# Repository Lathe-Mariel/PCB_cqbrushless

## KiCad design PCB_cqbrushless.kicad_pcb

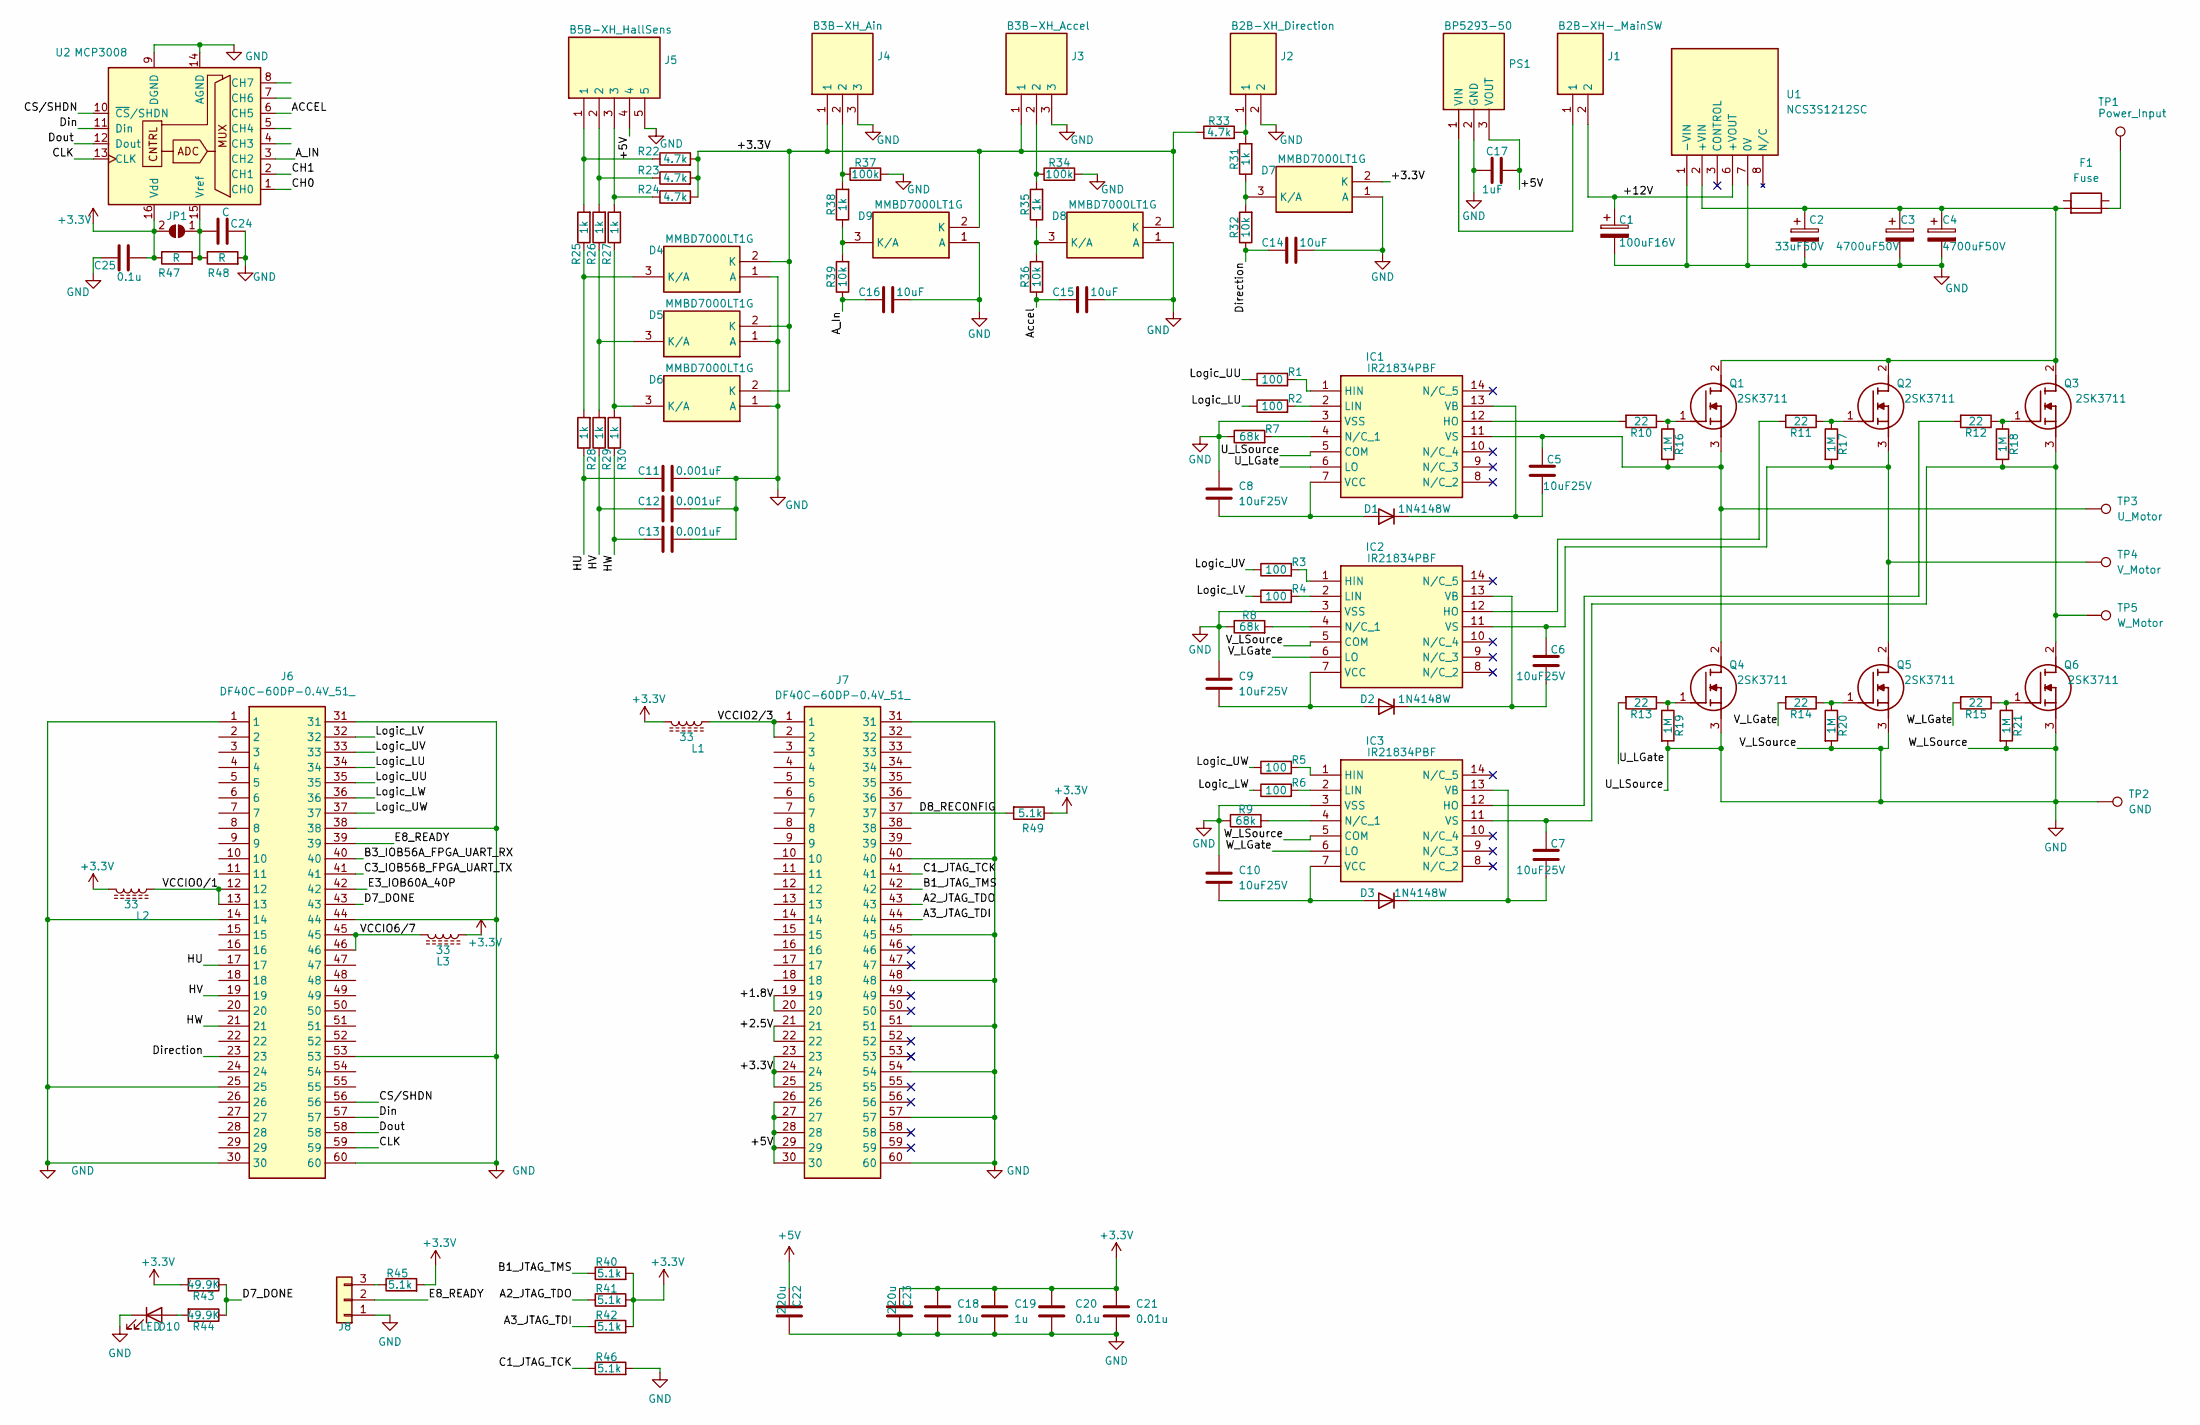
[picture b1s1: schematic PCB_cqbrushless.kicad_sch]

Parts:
C1: 100uF16V; CP_Radial_D5.0mm_P2.00mm
C2: 33uF50V; CP_Radial_D5.0mm_P2.00mm
C3, C4: 4700uF50V; CP_Radial_D35.0mm_P10.00mm_SnapIn
C5, C6, C7, C8, C9, C10: 10uF25V; C_0603_1608Metric_Pad1.08x0.95mm_HandSolder
C11, C12, C13: 0.001uF; C_0603_1608Metric_Pad1.08x0.95mm_HandSolder
C14, C15, C16: 10uF; C_0603_1608Metric_Pad1.08x0.95mm_HandSolder
C17: 1uF; C_0603_1608Metric_Pad1.08x0.95mm_HandSolder
C18: 10u; C_1206_3216Metric_Pad1.33x1.80mm_HandSolder
C19: 1u; C_0603_1608Metric_Pad1.08x0.95mm_HandSolder
C20, C25: 0.1u; C_0603_1608Metric_Pad1.08x0.95mm_HandSolder
C21: 0.01u; C_0603_1608Metric_Pad1.08x0.95mm_HandSolder
C22, C23: 220u; C_1206_3216Metric_Pad1.33x1.80mm_HandSolder
C24: C; C_0603_1608Metric_Pad1.08x0.95mm_HandSolder
D1, D2, D3: 1N4148W; D_SOD-123
D4, D5, D6, D7, D8, D9: MMBD7000LT1G; SOT96P237X111-3N; Manufacturer_Part_Number MMBD7000LT1G
D10: LED; LED_0603_1608Metric_Pad1.05x0.95mm_HandSolder
F1: Fuse; Fuse_Holder
IC1, IC2, IC3: IR21834PBF; DIP762W56P254L1930H533Q14N; Manufacturer_Part_Number IR21834PBF
J1: B2B-XH-_MainSW; B2BXHAMLFSN; Manufacturer_Part_Number B2B-XH-AM(LF)(SN)
J2: B2B-XH_Direction; B2BXHAMLFSN; Manufacturer_Part_Number B2B-XH-AM(LF)(SN)
J3: B3B-XH_Accel; B3BXHALFSN; Manufacturer_Part_Number B3B-XH-A(LF)(SN)
J4: B3B-XH_Ain; B3BXHALFSN; Manufacturer_Part_Number B3B-XH-A(LF)(SN)
J5: B5B-XH_HallSens; SHDR5W64P0X250_1X5_1490X575X700P; Manufacturer_Part_Number B5B-XH-A (LF)(SN)
J6, J7: DF40C-60DP-0.4V_51_; DF40C-60DP-0.4V(51); Manufacturer_Part_Number DF40C-60DP-0.4V(51)
J8: Conn_01x03; PinHeader_1x03_P2.54mm_Vertical
JP1: SolderJumper_2_Open; SolderJumper-2_P1.3mm_Open_TrianglePad1.0x1.5mm
L1, L2, L3: 33; L_0603_1608Metric_Pad1.05x0.95mm_HandSolder
PS1: BP5293-50; TO254P570X1700X1780-3P; Manufacturer_Part_Number BP5293-50
Q1, Q2, Q3, Q4, Q5, Q6: 2SK3711; TO545P500X1560X2410-3P; Manufacturer_Part_Number 2SK3711
R1, R2, R3, R4, R5, R6: 100; R_0603_1608Metric_Pad0.98x0.95mm_HandSolder
R7, R8, R9: 68k; R_0603_1608Metric_Pad0.98x0.95mm_HandSolder
R10, R11, R12, R13, R14, R15: 22; R_0603_1608Metric_Pad0.98x0.95mm_HandSolder
R16, R17, R18, R19, R20, R21: 1M; R_0603_1608Metric_Pad0.98x0.95mm_HandSolder
R22, R23, R24, R33: 4.7k; R_0603_1608Metric_Pad0.98x0.95mm_HandSolder
R25, R26, R27, R28, R29, R30, R31, R35, R38: 1k; R_0603_1608Metric_Pad0.98x0.95mm_HandSolder
R32, R36, R39: 10k; R_0603_1608Metric_Pad0.98x0.95mm_HandSolder
R34, R37: 100k; R_0603_1608Metric_Pad0.98x0.95mm_HandSolder
R40, R41, R42, R45, R46, R49: 5.1k; R_0603_1608Metric_Pad0.98x0.95mm_HandSolder
R43, R44: 49.9K; R_0603_1608Metric_Pad0.98x0.95mm_HandSolder
R47, R48: R; R_0603_1608Metric_Pad0.98x0.95mm_HandSolder
TP1: Power_Input; MountingHole_3.7mm_Pad
TP2: GND; MountingHole_3.7mm_Pad
TP3: U_Motor; MountingHole_3.7mm_Pad
TP4: V_Motor; MountingHole_3.7mm_Pad
TP5: W_Motor; MountingHole_3.7mm_Pad
U1: NCS3S1212SC; NCS3; Manufacturer_Part_Number NCS3S1212SC
U2: MCP3008; DIP-16_W7.62mm

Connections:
+3.3V: C18.1, C19.1, C20.1, C21.1, C23.1, C25.1, D4.2 (K), D5.2 (K), D6.2 (K), D7.2 (K), D8.2 (K), D9.2 (K), J3.1, J4.1, J7.23, J7.24, J7.25, JP1.2 (B), L1.2, L2.2, L3.1, R22.2, R23.2, R24.2, R33.1, R40.2, R41.2, R42.2, R43.2, R45.2, R47.1, R49.1, U2.16 (Vdd)
+5V: C17.1, C22.1, J5.4, J7.26, J7.27, J7.28, J7.29, J7.30, PS1.3 (VOUT)
/+12V: C1.1, J1.2, U1.6 (+VOUT)
/A2_JTAG_TDO: J7.43, R41.1
/A3_JTAG_TDI: J7.44, R42.1
/ACCEL: U2.6 (CH5)
/A_IN: U2.3 (CH2)
/A_In: C16.2, R39.1
/Accel: C15.2, R36.1
/B1_JTAG_TMS: J7.42, R40.1
/C1_JTAG_TCK: J7.41, R46.1
/CH0: U2.1 (CH0)
/CH1: U2.2 (CH1)
/CLK: J6.59, U2.13 (CLK)
/CS/SHDN: J6.56, U2.10 (~CS/SHDN)
/D7_DONE: J6.43, R43.1, R44.1
/D8_RECONFIG: J7.37, R49.2
/Din: J6.57, U2.11 (Din)
/Direction: C14.2, J6.23, R32.1
/Dout: J6.58, U2.12 (Dout)
/E8_READY: J6.39, J8.2
/HU: C11.2, J6.17, R28.1
/HV: C12.2, J6.19, R29.1
/HW: C13.2, J6.21, R30.1
/Logic_LU: J6.34, R2.1
/Logic_LV: J6.32, R4.1
/Logic_LW: J6.36, R6.1
/Logic_UU: J6.35, R1.1
/Logic_UV: J6.33, R3.1
/Logic_UW: J6.37, R5.1
/U_LGate: IC1.6 (LO), R13.2
/VCCIO0/1: J6.12, J6.13, L2.1
/VCCIO2/3: J7.1, J7.2, L1.1
/VCCIO6/7: J6.45, J6.46, L3.2
/V_LGate: IC2.6 (LO), R14.2
/W_LGate: IC3.6 (LO), R15.2
GND: C1.2, C2.2, C3.2, C4.2, C8.1, C9.1, C10.1, C11.1, C12.1, C13.1, C14.1, C15.1, C16.1, C17.2, C18.2, C19.2, C20.2, C21.2, C22.2, C23.2, C24.2, C25.2, D4.1 (A), D5.1 (A), D6.1 (A), D7.1 (A), D8.1 (A), D9.1 (A), D10.1 (K), IC1.3 (VSS), IC1.5 (COM), IC2.3 (VSS), IC2.5 (COM), IC3.3 (VSS), IC3.5 (COM), J2.2, J3.3, J4.3, J5.5, J6.1, J6.14, J6.25, J6.30, J6.31, J6.38, J6.44, J6.53, J6.60, J7.31, J7.40, J7.45, J7.48, J7.51, J7.54, J7.57, J7.60, J8.1, PS1.2 (GND), Q4.3 (S), Q5.3 (S), Q6.3 (S), R7.1, R8.1, R9.1, R19.2, R20.2, R21.2, R34.2, R37.2, R46.2, R48.2, TP2.1, U1.1 (-VIN), U1.7 (0V), U2.9 (DGND), U2.14 (AGND)
unnamed: C8.2, D1.2 (A), IC1.7 (VCC)
unnamed: C5.2, D1.1 (K), IC1.13 (VB)
unnamed: C9.2, D2.2 (A), IC2.7 (VCC)
unnamed: C6.2, D2.1 (K), IC2.13 (VB)
unnamed: C10.2, D3.2 (A), IC3.7 (VCC)
unnamed: C7.2, D3.1 (K), IC3.13 (VB)
unnamed: D4.3 (K/A), R25.1, R28.2
unnamed: D5.3 (K/A), R26.1, R29.2
unnamed: D6.3 (K/A), R27.1, R30.2
unnamed: D7.3 (K/A), R31.1, R32.2
unnamed: D8.3 (K/A), R35.1, R36.2
unnamed: D9.3 (K/A), R38.1, R39.2
unnamed: D10.2 (A), R44.2
unnamed: F1.3, TP1.1
unnamed: IC1.1 (HIN), R1.2
unnamed: IC1.12 (HO), R10.2
unnamed: IC1.2 (LIN), R2.2
unnamed: IC1.4 (N/C_1), R7.2
unnamed: C5.1, IC1.11 (VS), Q1.3 (S), Q4.2 (D), R16.2, TP3.1
unnamed: IC2.1 (HIN), R3.2
unnamed: IC2.12 (HO), R11.2
unnamed: IC2.2 (LIN), R4.2
unnamed: IC2.4 (N/C_1), R8.2
unnamed: C6.1, IC2.11 (VS), Q2.3 (S), Q5.2 (D), R17.2, TP4.1
unnamed: IC3.1 (HIN), R5.2
unnamed: IC3.12 (HO), R12.2
unnamed: IC3.2 (LIN), R6.2
unnamed: IC3.4 (N/C_1), R9.2
unnamed: C7.1, IC3.11 (VS), Q3.3 (S), Q6.2 (D), R18.2, TP5.1
unnamed: J2.1, R31.2, R33.2
unnamed: J3.2, R34.1, R35.2
unnamed: J4.2, R37.1, R38.2
unnamed: J5.1, R22.1, R25.2
unnamed: J5.2, R23.1, R26.2
unnamed: J5.3, R24.1, R27.2
unnamed: J7.19, J7.20
unnamed: J7.21, J7.22
unnamed: J8.3, R45.1
unnamed: C24.1, JP1.1 (A), R47.2, R48.1, U2.15 (Vref)
unnamed: J1.1, PS1.1 (VIN)
unnamed: C2.1, C3.1, C4.1, F1.1, Q1.2 (D), Q2.2 (D), Q3.2 (D), U1.2 (+VIN)
unnamed: Q1.1 (G), R10.1, R16.1
unnamed: Q2.1 (G), R11.1, R17.1
unnamed: Q3.1 (G), R12.1, R18.1
unnamed: Q4.1 (G), R13.1, R19.1
unnamed: Q5.1 (G), R14.1, R20.1
unnamed: Q6.1 (G), R15.1, R21.1

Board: 2 copper layers, 112 parts (6 on the bottom side), 59 nets, no tracks yet.

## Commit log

2024-09-20 0920
2024-09-25 0925
2024-10-02 1003
2024-10-07 1007
